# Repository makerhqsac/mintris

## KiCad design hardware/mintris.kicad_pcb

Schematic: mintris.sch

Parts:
BT1: Battery_Cell; BAT-HLD-001-THM
BTN1: LEFT; SW_PUSH_6mm
BTN2: MID; SW_PUSH_6mm
BTN3: RIGHT; SW_PUSH_6mm
J1: ICSP; PinHeader_2x03_P2.54mm_Vertical
J2: OLED; PinHeader_1x04_P2.54mm_Vertical
R1, R2, R3: R; R_Axial_DIN0207_L6.3mm_D2.5mm_P7.62mm_Horizontal
SW1: SW_SPDT; SK12D07
U1: ATTINY; DIP-8_W7.62mm

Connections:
/LEFT: BTN1.1, J1.1, R1.1, U1.6 (PB1)
/MID: BTN2.1, J1.3, R2.1, U1.7 (PB2)
/RIGHT: BTN3.1, J1.4, R3.1, U1.5 (AREF/PB0)
/RST: J1.5, U1.1 (~RESET~/PB5)
/SCL: J2.3, U1.3 (XTAL2/PB4)
/SDA: J2.4, U1.2 (XTAL1/PB3)
GND: BT1.2, J1.6, J2.2, R1.2, R2.2, R3.2, U1.4 (GND)
unnamed: BT1.1, SW1.2
VCC: BTN1.2, BTN2.2, BTN3.2, J1.2, J2.1, SW1.3, U1.8 (VCC)

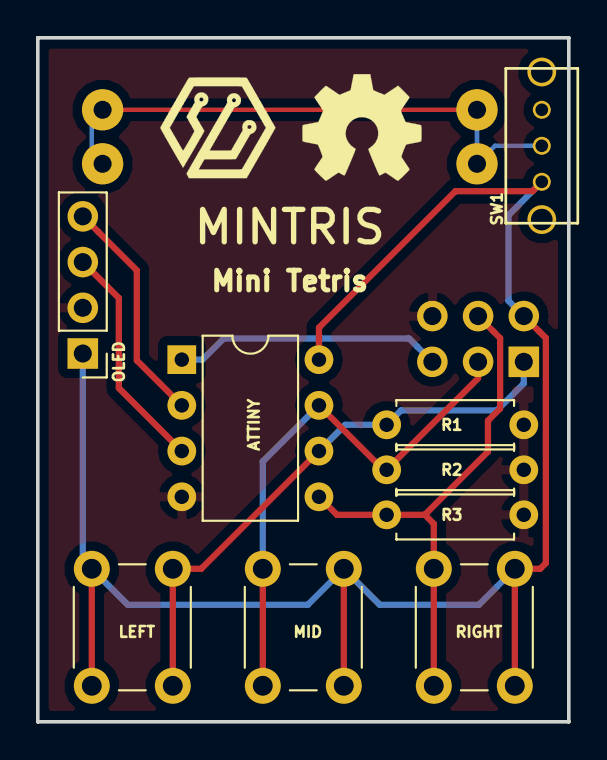
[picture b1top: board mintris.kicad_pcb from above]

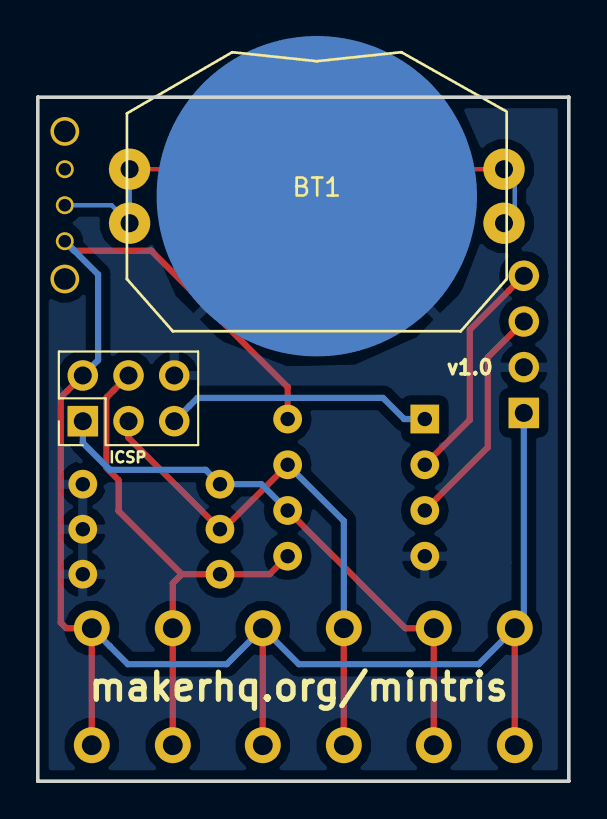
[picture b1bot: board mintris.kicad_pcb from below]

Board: 2 copper layers, 29.5 x 38.0 mm, 11 parts (2 on the bottom side), 9 nets.

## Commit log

2018-11-01 Add enclosure
2018-11-12 improve latching mechanism
